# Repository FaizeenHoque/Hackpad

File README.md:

# Hackpad
Hackpad for macros!

Hackpad built by FaixeN for Hack Club’s Blueprint Program. It features a fully modular design with four Cherry MX–style switch slots and two SK6812MINI addressable LEDs.

### Features
1. 4 Cherry MX-Style Keys
2. 2 Mini RGB LEDS

### CAD Model

### PCB
Heres the PCB that will be used for the project

### Assembled

### Build

**Case doesnt fit!

### Firmware
This hackpad uses QMK firmware for everything. 

### BOM:

Here should be everything you need to make this hackpad:
2x SK6812MINI
4x SW_Cherry_MX
1x XIAO-RP2040-DIP

### Extra stuff:
I want to keep updating this project here and there, maybe add a screen in the future and add a potentiometer for volume control.
this the first time i have created a pcb and a 3d model for printing, look forward to make more cool stuff in the future

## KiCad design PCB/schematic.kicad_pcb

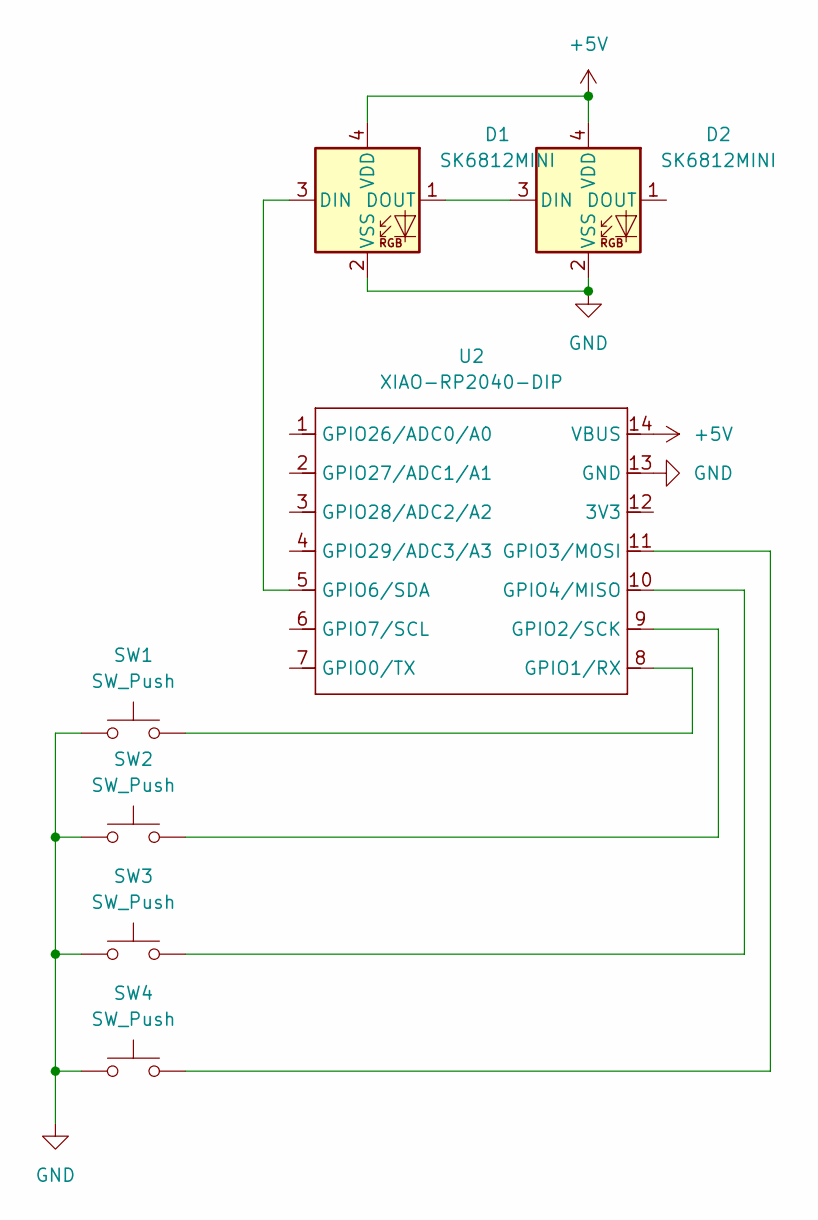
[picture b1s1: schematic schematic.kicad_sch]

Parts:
D1, D2: SK6812MINI; LED_SK6812MINI_PLCC4_3.5x3.5mm_P1.75mm
SW1, SW2, SW3, SW4: SW_Push; SW_Cherry_MX_1.00u_PCB
U2: XIAO-RP2040-DIP

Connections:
+5V: D1.4 (VDD), D2.4 (VDD), U2.14 (VBUS)
GND: D1.2 (VSS), D2.2 (VSS), SW1.1, SW2.1, SW3.1, SW4.1, U2.13 (GND)
unnamed: D1.3 (DIN), U2.5 (GPIO6/SDA)
unnamed: D1.1 (DOUT), D2.3 (DIN)
unnamed: SW1.2, U2.8 (GPIO1/RX)
unnamed: SW2.2, U2.9 (GPIO2/SCK)
unnamed: SW4.2, U2.11 (GPIO3/MOSI)
unnamed: SW3.2, U2.10 (GPIO4/MISO)

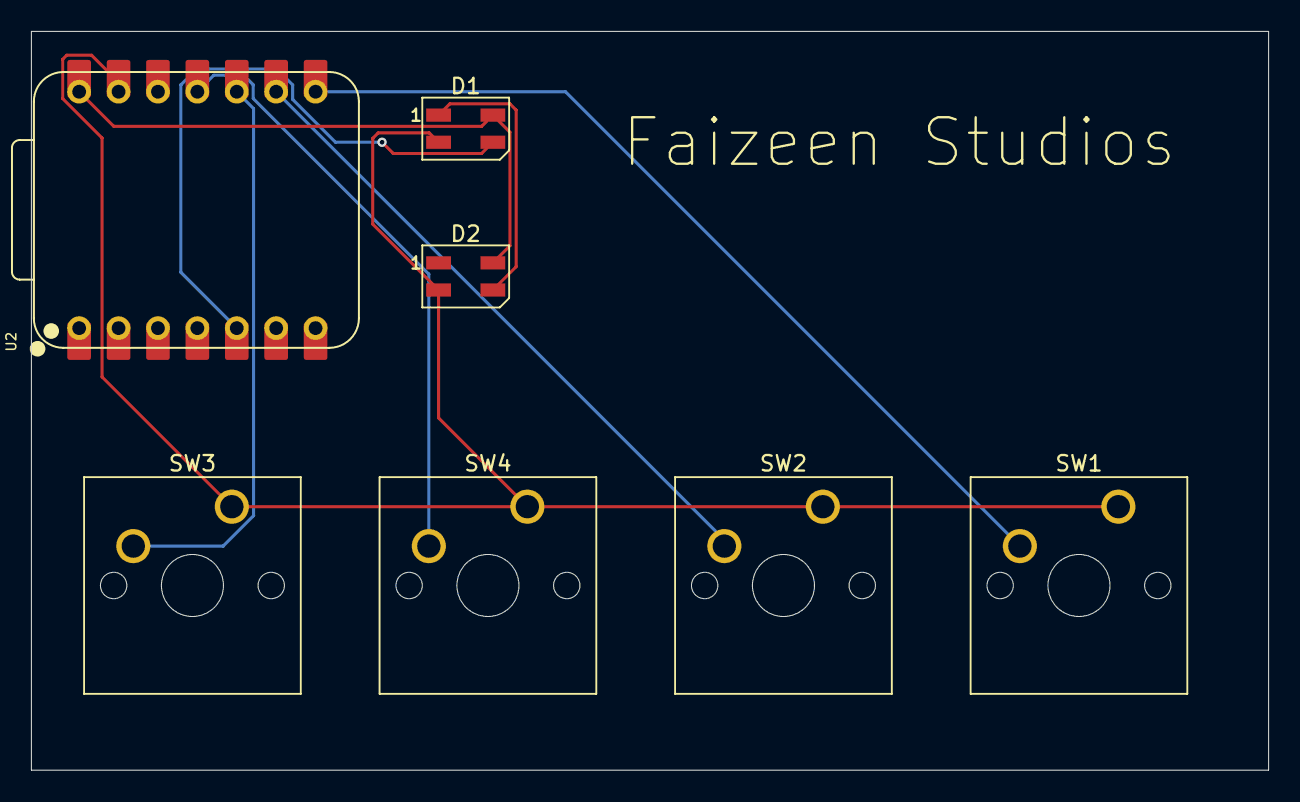
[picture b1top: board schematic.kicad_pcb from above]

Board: 2 copper layers, 79.8 x 47.6 mm, 7 parts (0 on the bottom side), 8 nets.

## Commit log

2025-12-03 Add 'Assembled' section with image to README
    Added a new section 'Assembled' with an image to the README.
